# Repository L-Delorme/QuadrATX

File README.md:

# QuadrATX
ATX mod for the Macintosh Quadra 900/950

This is a work in progress mod. The AC Board has not been fully tested. Use at your own risk.
The BOM has not been finalized. 
Instructions on how to build a QuadrATX kit will follow. 

Hardware protected by CC-BY-NC-SA-4.0 (Attribution-NonCommercial-ShareAlike)
https://creativecommons.org/licenses/by-nc-sa/4.0/

If you wish to sell this product, please contact me beforehand. 
theapplechronicles AT gmail DOT com

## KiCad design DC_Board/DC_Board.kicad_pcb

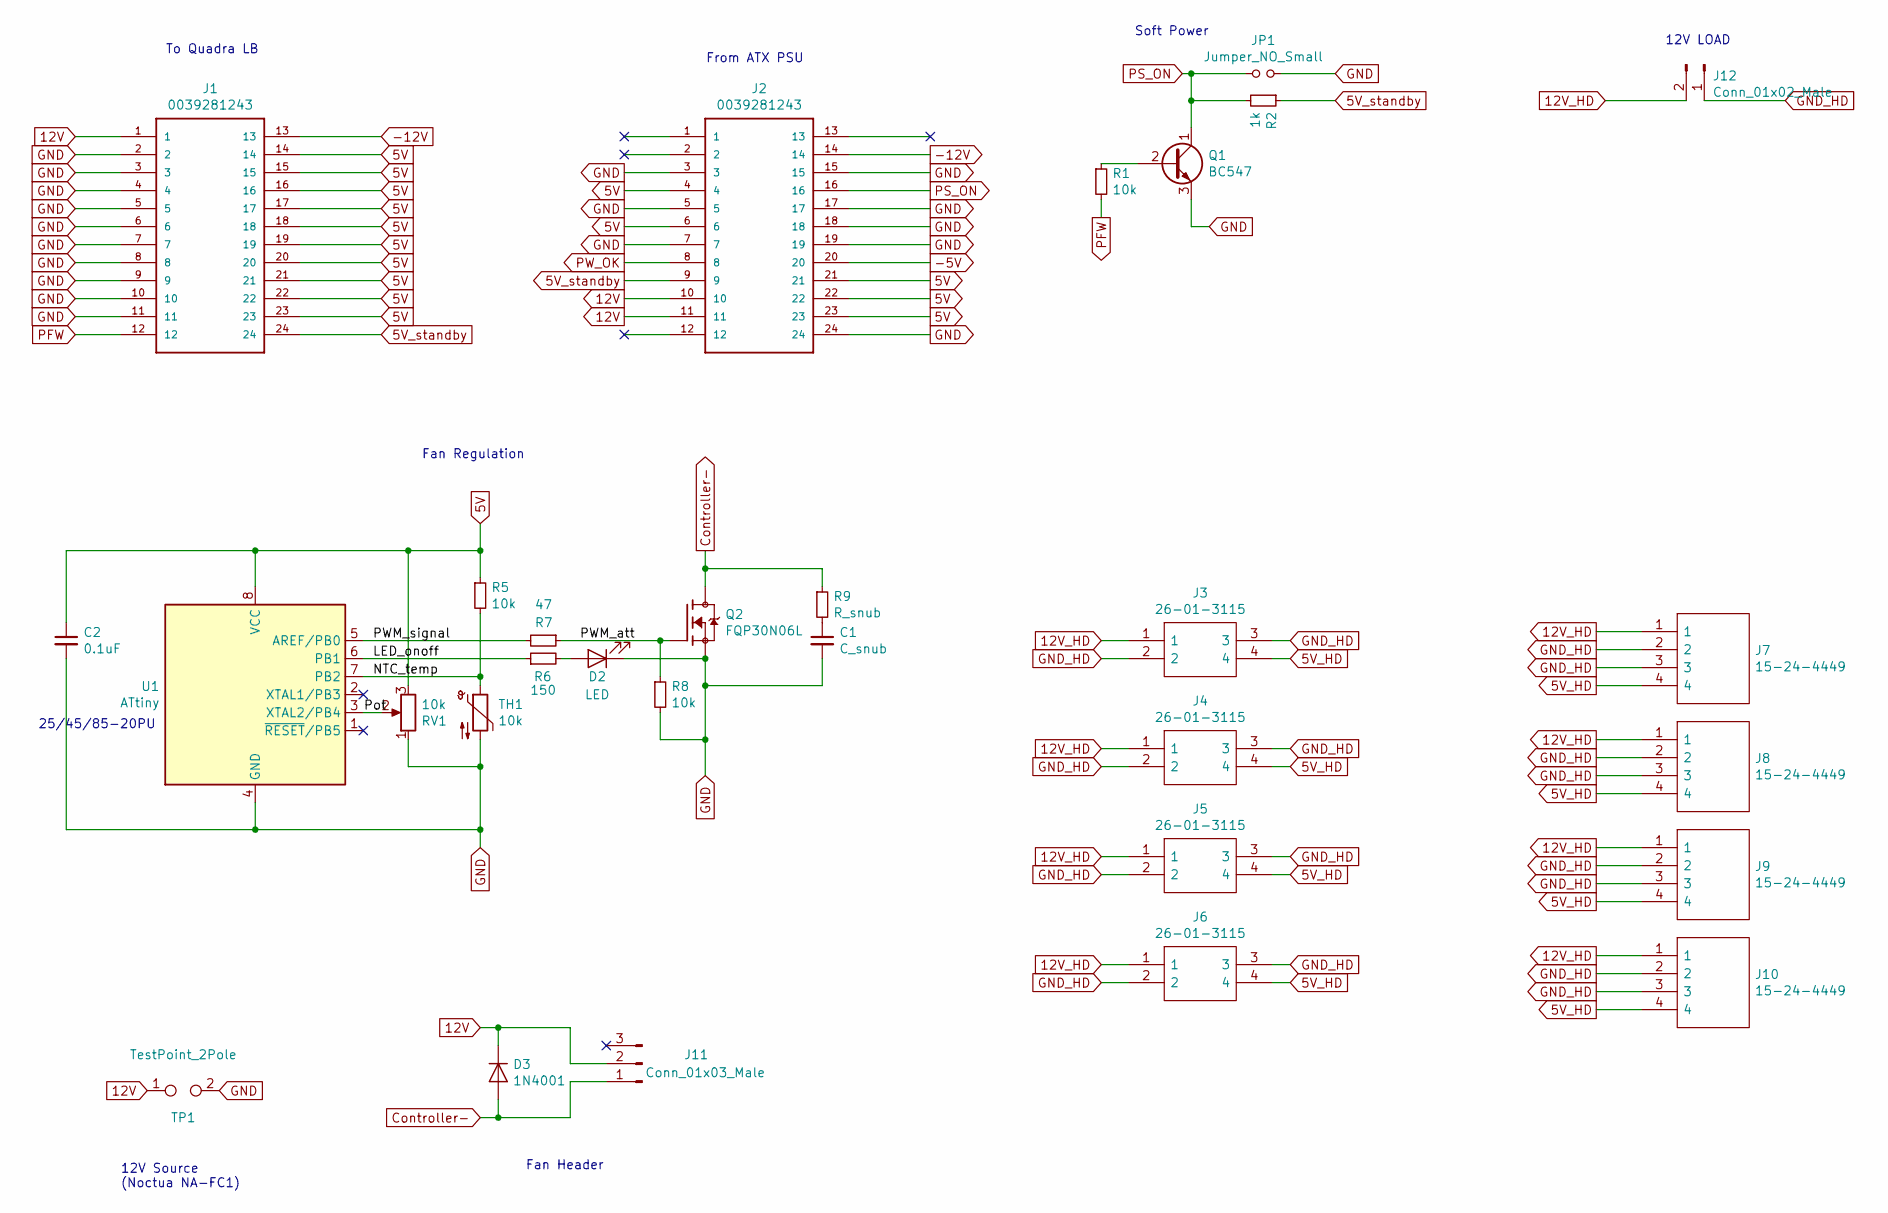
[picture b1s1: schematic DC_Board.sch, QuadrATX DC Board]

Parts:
C1: C_snub; C_Rect_L9.0mm_W2.5mm_P7.50mm_MKT
C2: 0.1uF; C_Disc_D4.7mm_W2.5mm_P5.00mm
D2: LED; LED_D5.0mm
D3: 1N4001; D_DO-41_SOD81_P10.16mm_Horizontal
J1: 0039281243; Molex_Mini-Fit_Jr_5566-24A2_2x12_P4.20mm_Vertical
J2: 0039281243; Molex_Mini-Fit_Jr_5566-24A_2x12_P4.20mm_Vertical
J3, J4, J5, J6: 26-01-3115; 39-30-1040; Manufacturer_Part_Number 26-01-3115; Mouser Part Number 538-26-01-3115
J7, J8, J9, J10: 15-24-4449; 641737-1; Manufacturer_Part_Number 15-24-4449; Mouser Part Number 538-15-24-4449
J11: Conn_01x03_Male; Molex_KK-254_AE-6410-03A_1x03_P2.54mm_Vertical
J12: Conn_01x02_Male; Molex_KK-396_A-41791-0002_1x02_P3.96mm_Vertical
JP1: Jumper_NO_Small; PinSocket_1x02_P2.54mm_Vertical
Q1: BC547; TO-92L_Wide
Q2: FQP30N06L; TO-220F-3_Horizontal_TabDown
R1, R5, R8: 10k; R_Axial_DIN0309_L9.0mm_D3.2mm_P15.24mm_Horizontal
R2: 1k; R_Axial_DIN0309_L9.0mm_D3.2mm_P15.24mm_Horizontal
R6: 150; R_Axial_DIN0309_L9.0mm_D3.2mm_P15.24mm_Horizontal
R7: 47; R_Axial_DIN0309_L9.0mm_D3.2mm_P15.24mm_Horizontal
R9: R_snub; R_Axial_DIN0309_L9.0mm_D3.2mm_P15.24mm_Horizontal
RV1: 10k; 3386P-1-103LF
TH1: 10k; R_Axial_DIN0309_L9.0mm_D3.2mm_P15.24mm_Horizontal
TP1: TestPoint_2Pole; PinHeader_2x01_P2.54mm_Vertical
U1: ATtiny; DIP-8_W7.62mm

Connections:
5V: C2.1, J1.14, J1.15, J1.16, J1.17, J1.18, J1.19, J1.20, J1.21, J1.22, J1.23, J2.4, J2.6, J2.21, J2.22, J2.23, R5.1, RV1.3, U1.8 (VCC)
5V_HD: J3.4, J4.4, J5.4, J6.4, J7.4, J8.4, J9.4, J10.4
5V_standby: J1.24, J2.9, R2.1
12V: D3.1 (K), J1.1, J2.10, J2.11, J11.2, TP1.1
12V_HD: J3.1, J4.1, J5.1, J6.1, J7.1, J8.1, J9.1, J10.1, J12.2
-5V: J2.20
-12V: J1.13, J2.14
/LED_onoff: R6.1, U1.6 (PB1)
/NTC_temp: R5.2, TH1.1, U1.7 (PB2)
/PWM_att: Q2.1, R7.1, R8.1
/PWM_signal: R7.2, U1.5 (AREF/PB0)
/Pot: RV1.2, U1.3 (XTAL2/PB4)
Controller-: D3.2 (A), J11.1, Q2.2, R9.1
GND: C1.2, C2.2, D2.1 (K), J1.2, J1.3, J1.4, J1.5, J1.6, J1.7, J1.8, J1.9, J1.10, J1.11, J2.3, J2.5, J2.7, J2.15, J2.17, J2.18, J2.19, J2.24, JP1.2, Q1.3 (E), Q2.3, R8.2, RV1.1, TH1.2, TP1.2, U1.4 (GND)
GND_HD: J3.2, J3.3, J4.2, J4.3, J5.2, J5.3, J6.2, J6.3, J7.2, J7.3, J8.2, J8.3, J9.2, J9.3, J10.2, J10.3, J12.1
unnamed: C1.1, R9.2
unnamed: D2.2 (A), R6.2
unnamed: Q1.2 (B), R1.1
PFW: J1.12, R1.2
PS_ON: J2.16, JP1.1, Q1.1 (C), R2.2
PW_OK: J2.8

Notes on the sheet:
From ATX PSU
Soft Power
12V LOAD
To Quadra LB
Fan Regulation
25/45/85-20PU
12V Source (Noctua NA-FC1)
Fan Header

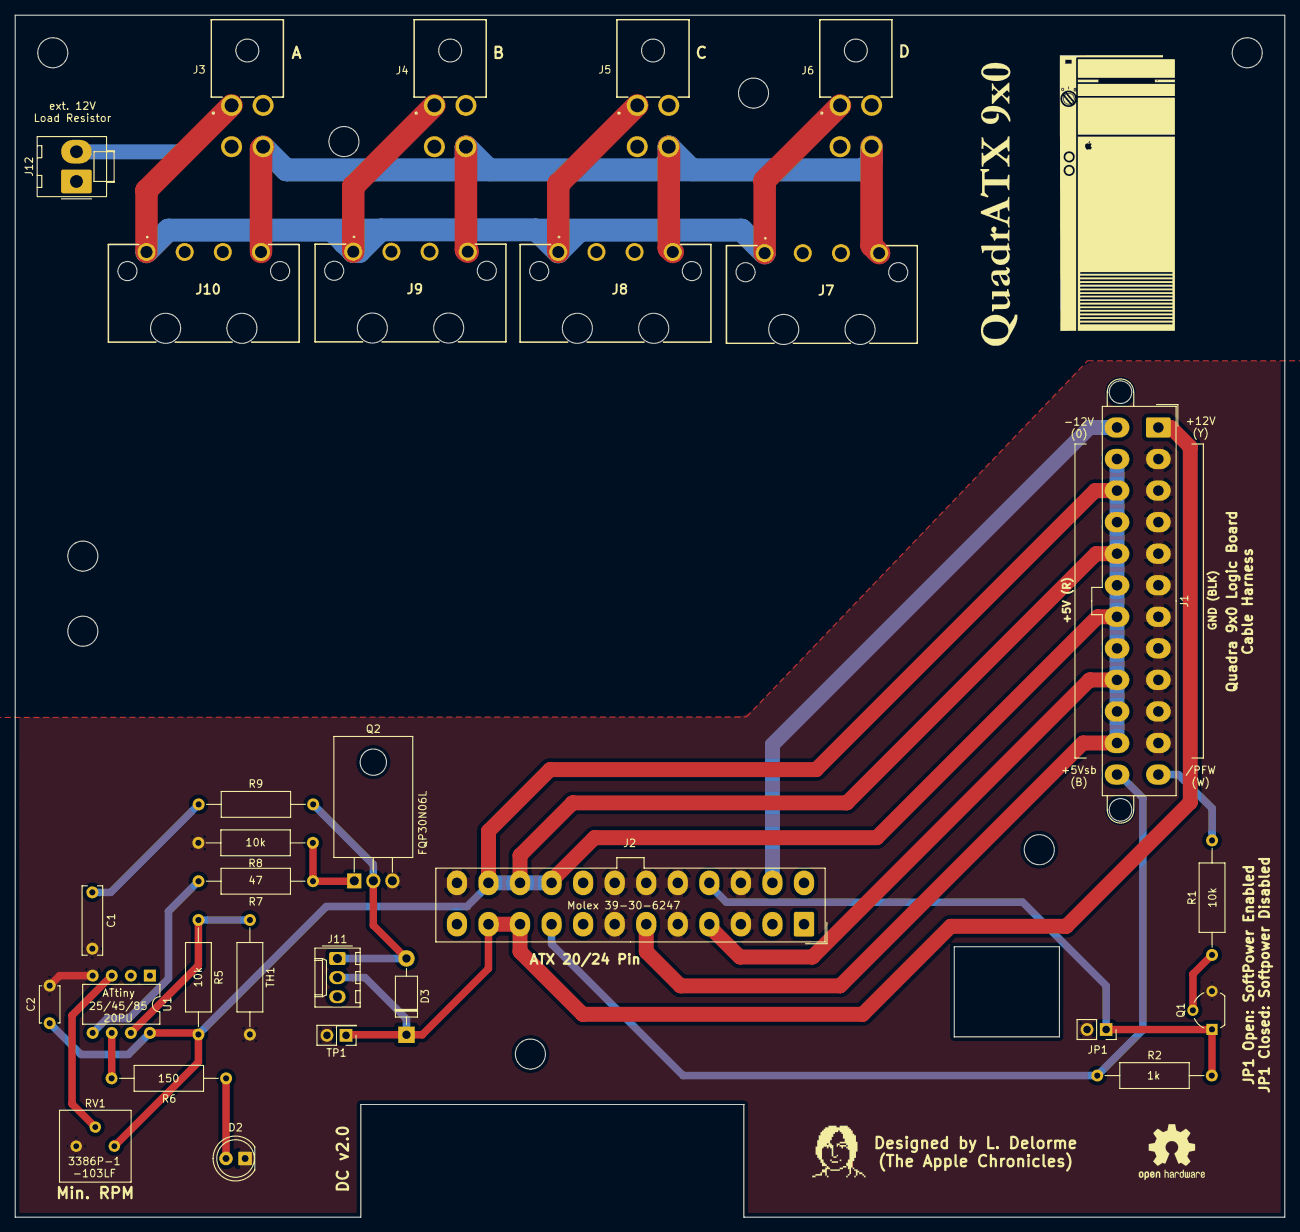
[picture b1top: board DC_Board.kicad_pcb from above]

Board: 2 copper layers, 169.0 x 160.0 mm, 30 parts (0 on the bottom side), 19 nets.

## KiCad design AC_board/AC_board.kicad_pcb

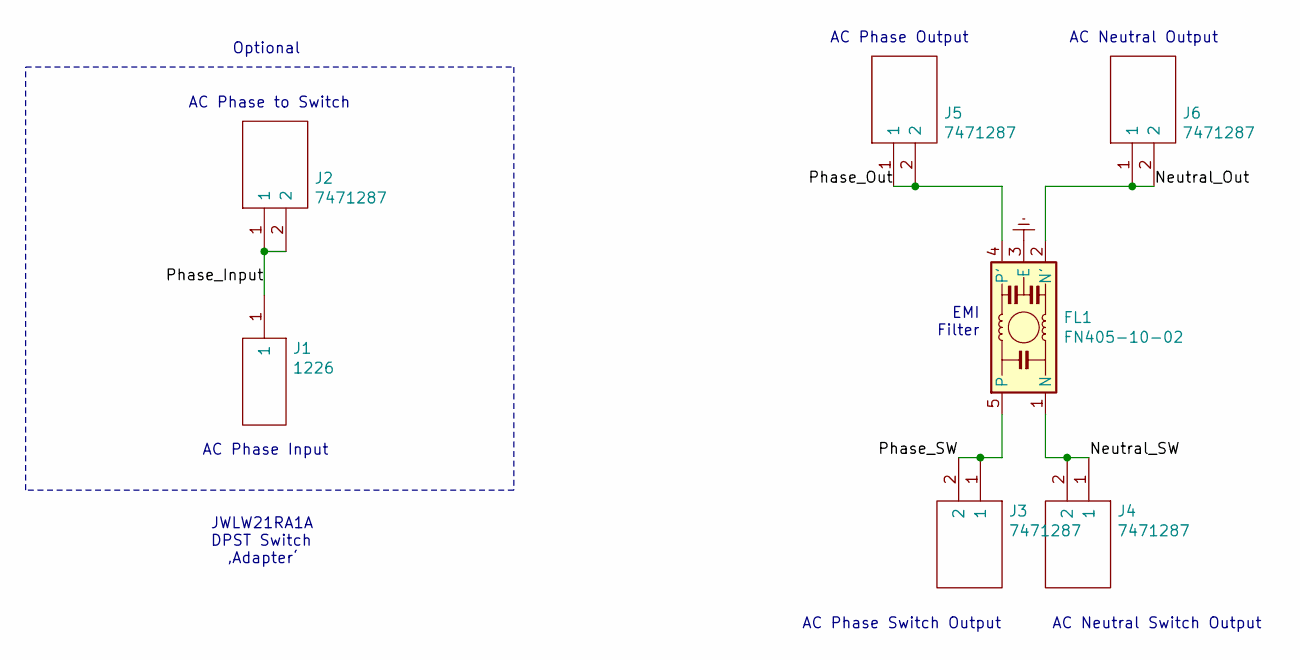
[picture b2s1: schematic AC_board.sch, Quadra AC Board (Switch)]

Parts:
FL1: FN405-10-02; Filter_Schaffner_FN405
J1: 1226; JST_LV; Manufacturer_Part_Number 1226; Mouser Part Number 534-1226
J2, J3, J4, J5, J6: 7471287; 7471287_large; Manufacturer_Part_Number 7471287; Mouser Part Number 710-7471287

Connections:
/Neutral_Out: FL1.2 (N'), J6.1, J6.2
/Neutral_SW: FL1.1 (N), J4.1, J4.2
/Phase_Input: J1.1, J2.1, J2.2
/Phase_Out: FL1.4 (P'), J5.1, J5.2
/Phase_SW: FL1.5, J3.1, J3.2
Earth: FL1.3 (E)

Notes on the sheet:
EMI Filter
AC Neutral Output
AC Phase Output
AC Phase Input
AC Neutral Switch Output
JWLW21RA1A DPST Switch ‚Adapter‘
AC Phase Switch Output
AC Phase to Switch
Optional

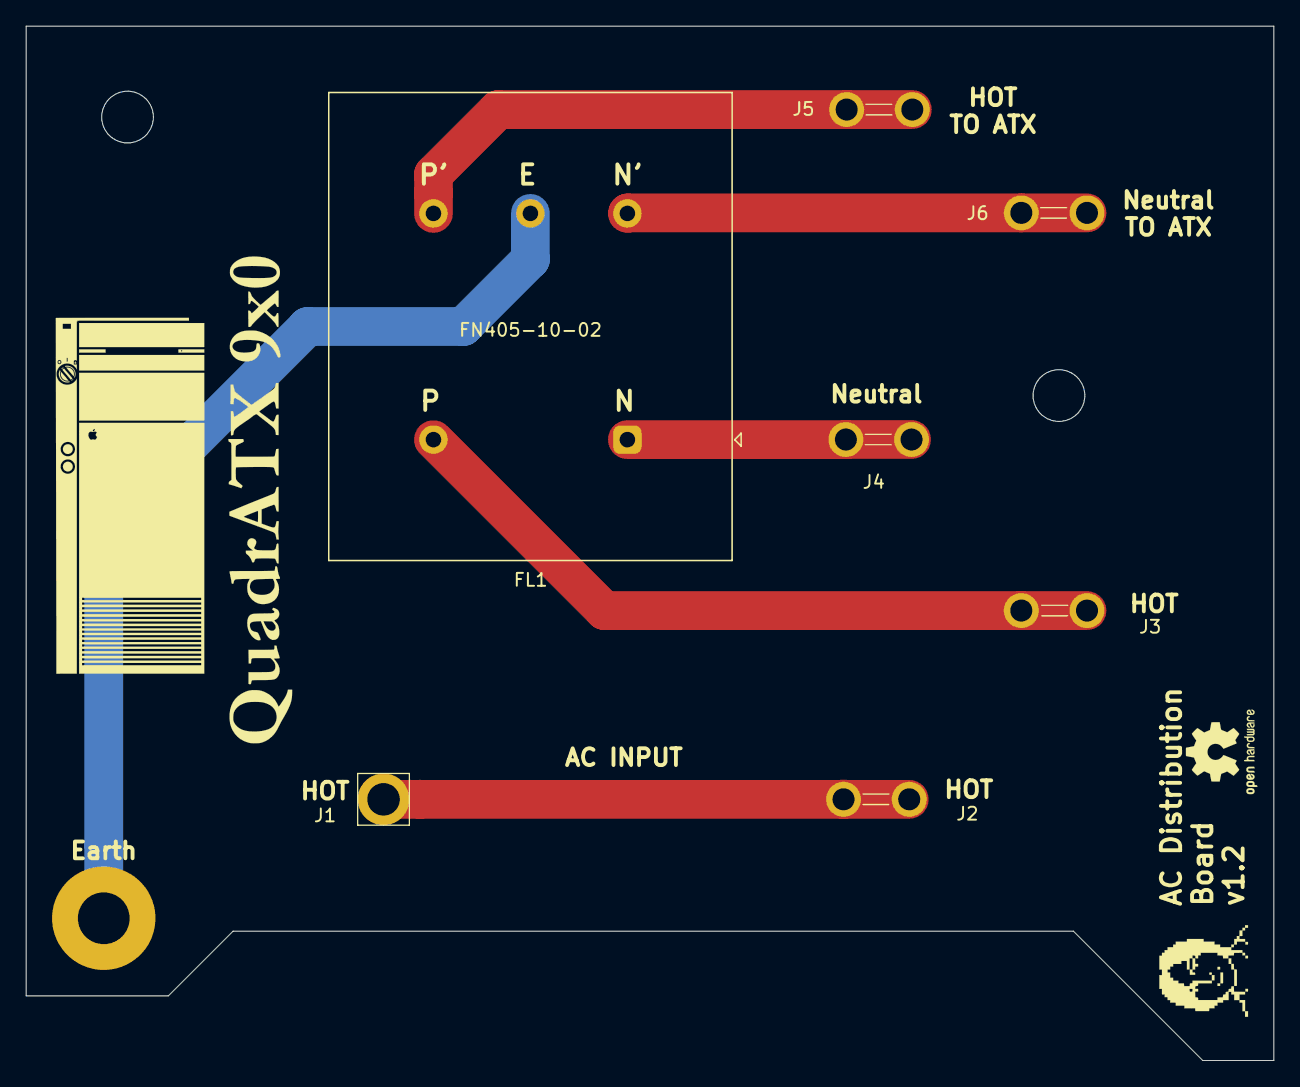
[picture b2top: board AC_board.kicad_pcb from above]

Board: 2 copper layers, 96.5 x 80.0 mm, 7 parts (0 on the bottom side), 5 nets.

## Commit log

2020-11-16 Removed all .DS_Store files
2020-11-16 Updated AC Gerbers
2020-11-16 Create LICENSE
2020-11-16 Fan controller files
2023-03-12 Brand new AC and DC boards

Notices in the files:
AC_board/AC_board.kicad_pcb:
License: CC BY 4.0
AC_board/AC_board.sch:
creativecommons.org/licenses/by/4.0
